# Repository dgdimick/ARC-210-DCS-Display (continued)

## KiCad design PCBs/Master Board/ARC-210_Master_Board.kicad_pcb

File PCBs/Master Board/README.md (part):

# ARC-210 Main Board v1.1 and schematic

**Last updated: November 13, 2026 at 9:41 PM MST (America/Denver)**

Updated October 29, 2026: USB-powered design with TFT VCC supplied directly from the Teensy's 3.3 V rail.

## Download and open

Download this repository using **Code → Download ZIP**, extract it, and keep this entire folder together. Open `ARC-210_Master_Board.kicad_pro` in **KiCad 10**, then open the schematic or PCB Editor.

You can also download the [schematic](ARC-210_Master_Board.kicad_sch) and [PCB v1.1](ARC-210_Master_Board.kicad_pcb) directly. Downloading only that file does not include the project library configuration.

Main Board **v1.1** includes the completed placement and routing, GND copper pours on both layers, and a [Gerber/drill package](Manufacturing/Main-Board-PCB-v1.1-Gerbers-Drill.zip). Its switch mounting and anti-rotation cutouts, four 3.5 mm mounting holes and USB zip-tie slots are retained. All 13 circuit component footprints are on B.Cu, facing away from the faceplate. ERC, DRC and schematic/PCB parity pass under the saved settings, with zero unconnected items. I’ve checked the physical fit of Main Board v1.1; current verification, assembly and manufactured-board testing are still ahead. Take your time with the build. If you get stuck, I’m happy to help in [Discussions](https://github.com/dgdimick/ARC-210-DCS-Display/discussions) if you need a hand.

## PCB layout — five or six boards

The panel uses **five required PCBs**: one Main Board, one Button Matrix, one Rotary Encoder, and two multi-position Rotary Switch boards, all controlled by one Teensy 4.1. An **optional SQL On/Off switch PCB brings the total to six**; it can be omitted when wiring directly to the switch’s solder lugs. The optional SQL board uses the same Rotary Switch PCB design.

The [shaft spacer v.5](../../Supporting%20STL%27s/Shaft_Spacer_v.5.stl) is **required in all installations** to support the longer SQL On/Off switch shaft, whether or not the optional PCB is fitted.

## Signals and connectors

- **J1:** TFT connector. See the [TFT cable mapping](../../parts/README.md#pin-headers-and-mating-connectors--october-12-2026); it is not a straight-through cable.
- **J2:** separate 4 × 4 button matrix; pins 1–4 use GPIO 30, 31, 32, 33, and pins 5–8 use GPIO 35, 36, 37, 40.
- **J4:** 14-pin rotary-encoder connector; pins 13 and 14 are GND.
- **J10 (MASTER) pin 2:** rotary-switch signal through R1 to GPIO 14 / A0, KiCad U1 pad 36.
- **J9 (MODE) pin 2:** rotary-switch signal through R2 to GPIO 15 / A1, KiCad U1 pad 37.
- **SQL1:** pin 1 is GPIO 41 / U1 pad 33; pin 2 is GND. The SQL On/Off switch PCB is optional when wiring its solder lugs directly. Dedicated **TP1 (SQL signal, GPIO 41 / U1 pad 33)** and **TP2 (GND)** solder-wire pads are now included in the Main Board schematic and PCB draft. The optional SQL1 header remains available. The pads are placed and routed in the current draft; I’ve checked the physical fit of Main Board v1.1; I still need to check the assembled board.

**GPIO labels are not KiCad pad numbers.** For example, GPIO 4 is U1 pad 6, GPIO 14 is pad 36, and GPIO 15 is pad 37. Use the labels printed on the Teensy for wiring and firmware; use the matching symbol and `teensy:Teensy41` footprint when updating the PCB.

## USB cable zip-tie slots

**Added October 29, 2026:** The PCB includes two **4 × 2 mm oblong internal cutouts** below the Teensy's USB connector. Their centers align with the two Teensy pin rows, at X = 128.21 mm and 143.45 mm, Y = 163.50 mm in the KiCad board coordinates. The long direction follows the pin rows/cable direction.

The slots are intended for a small **2.5 mm zip tie** to hold the USB cable against the PCB and reduce strain on the Teensy's Micro-B connector. They are milled cutouts on **Edge.Cuts**, with no electrical pads. The existing routing and component positions are unchanged.

**Pending physical fit check:** Confirm the actual cable plug, boot, and tie fit before final assembly. Secure the cable without loading the USB connector, leave service slack, and avoid overtightening. Final cable support validation and any additional printed support remain pending. Main Board v1.1 fabrication files are published; the physical strain-relief check remains pending.

The updated DRC/parity report shows **zero violations, zero unconnected items, and zero schematic/PCB mismatches** under the saved settings.

## Required Rotary Encoder spacers

Print **six [Rotary Encoder spacers v.1](../../Supporting%20STL%27s/Rotary_Encoder_Spacer_v.1.stl)**, one for each encoder, to center the encoder threads in the faceplate holes.

## SQL On/Off rotary switch support

Use the [shaft support spacer v.5](../../Supporting%20STL%27s/Shaft_Spacer_v.5.stl) in **all installations** to support the **longer shaft used by the SQL On/Off rotary switch**. Fit the spacer whether using the optional switch PCB or wiring directly to the switch's solder lugs.

## Channel and SQL knobs

**The 17-part set has passed test fitting at 100% scale, with Channel v4.2 separately reprinted and confirmed after the earlier complete-layout test. The combined downloads now include that replacement.** Please keep checking [Project Updates](../../Docs/Project-Updates.md) for changes.

[Channel knob v4.2](../../Supporting%20STL%27s/Channel_Knob_v.4.2.stl) · [SQL knob v1.2](../../Supporting%20STL%27s/SQL_Knob_v.1.2.stl)

**Channel v4.2 and SQL v1.2 have the same outside size and small side hole, but different shaft holes.** Print one of each at 100% scale. I’ve test-fitted both; see the [STL README](../../Supporting%20STL%27s/README.md) for the socket details and current downloads.

The SQL shaft support spacer v.5 remains required in all installations.

## Power and lighting

The Teensy is powered by USB, and **TFT VCC connects directly to the Teensy's 3.3 V rail** (`TEENSY_3V3`, U1 pad 15). I’ve tested the TFT at 3.3 V and found the brightness satisfactory. I removed the external protected 5 V input and Main Board JP1 power selector. I removed C5 (470 µF) and C6 (0.1 µF) to match the direct Teensy-to-TFT wiring I tested. C1/C2 and R1/R2 remain as the rotary-input filters. Keep total external 3.3 V consumption within PJRC's recommended 250 mA maximum; brightness confirmation is not a current measurement.

Removed from the schematic and PCB: **J3, F2, D1, D2, D3, Q2, R15, R16, R17, JP1, C5, and C6**. There is no external input jack, fuse, SCR/zener protection branch, power indicator LED, or TFT power-selector shunt in this revision. This does not affect the separate rotary-switch PCB's JP1 solder bridge.

C5 (470 µF) and C6 (0.1 µF) have been removed from the schematic, PCB, and BOM to match the tested direct TFT wiring. No additional TFT supply capacitors are fitted on this Main Board. C1/C2 and R1/R2 remain as the rotary-input filters. The TFT backlight-control signal remains connected to GPIO 4.

**The current Button Matrix PCB v3.2 does not support LED backlighting.** I would need to redesign it and the Main Board and use light-transmitting buttons. There is no finished design or release date. The TFT backlight is separate; see [Future Thoughts](../../Docs/Future-Thoughts.md) for clearance, power, possible four-layer costs, and reusable-part plans.

My aim is to reuse the **rotary encoders, rotary switches, socket-mounted Teensy, faceplate, and other compatible parts outside the two replacement boards**. I still need to check compatibility during the redesign. Male Teensy headers and matching Main Board sockets would let you move the controller to a compatible replacement board. Illuminated legends would need suitable light-transmitting buttons.

## Rotary-switch test wiring

I tested both seven-position switches with their outputs connected directly to GPIO 14 and 15. They worked without the schematic's 220 Ω series resistors or 100 nF filter capacitors. The six 1 kΩ ladder resistors on each switch board were fitted and JP1 on each switch board was open. I saw voltage fluctuations on the TFT, but they did not affect the detected switch positions.

## Teensy 4.1 in the 3D Viewer

### Main PCB 3D preview

*October 28, 2026 — Main Board placement and routing in progress, viewed from the component side facing away from the faceplate.*

The current working layout includes the Teensy 4.1, TFT and control connectors, and SQL On/Off solder connections. **J9 is MODE** (GPIO 15 / A1), and **J10 is MASTER** (GPIO 14 / A0). A **26.2 mm circle**, centered on the SQL shaft hole, provides a switch-body spacing guide without electrical pads. The earlier board-edge silkscreen clipping warning is resolved in the corrected upload. The existing shaft opening, anti-rotation slot, and mounting holes are retained.

The current saved PCB and schematic shown by this layout-progress update are now uploaded to this folder. The v1.1 design checks pass under the saved settings. I’ve checked the physical fit of Main Board v1.1; I still need to complete verification. Main Board v1.1 design and fabrication files are now published; physical fit is confirmed and manufactured-board validation is still to come.

[Earlier angled Teensy 4.1 preview — October 27](../../images/Main-PCB-Teensy-3D.png)

The project includes [Teensy_4.1_Board.step](Libraries/3dmodels/Teensy_4.1_Board.step), already attached to **U1** in the Main PCB. Its model path is `${KIPRJMOD}/Libraries/3dmodels/Teensy_4.1_Board.step`, so it works after downloading or cloning the repository without a machine-specific path.

1. Download the repository ZIP or clone it, then extract/keep the entire Main Board project folder together.
2. Open `ARC-210_Master_Board.kicad_pro` and launch PCB Editor.
3. Open **View → 3D Viewer** (**Alt+3**).
4. Rotate to the back/underside: U1 and the other component bodies are on **B.Cu**, facing away from the faceplate.

If U1 is missing, check its **Footprint Properties → 3D Models** entry and confirm the STEP file is present at the path above. Reopen the viewer after replacing project files. The old missing assembly-model path and erroneous footprint-folder model entry have been removed.

I checked the model in bottom and angled renders. This verifies visibility and visual alignment; I’ve now checked the physical fit of Main Board v1.1. Final socket height and component clearances should still be checked during assembly. No electrical connections were changed by attaching the model.

## Included libraries and checks

- `Libraries/symbols/teensy.kicad_sym`: Teensy symbols; accompanying license included.
- `Libraries/symbols/ARC210_Power.kicad_sym`: C106D SCR symbol.
- `Libraries/teensy.pretty/Teensy41.kicad_mod`: matching Teensy 4.1 footprint.
- `ARC210_Custom.pretty`: historical custom footprints; the removed protection parts are no longer fitted.
- `sym-lib-table` and `fp-lib-table`: project-relative library paths.

Install KiCad's standard symbol, footprint, and 3D model libraries too. The Teensy 4.1 STEP model is now included and attached to U1; see the 3D Viewer section above.

October 29, 2026 checks after matching J4 and TP1 values: [ERC](ERC-report.json) reports **zero violations**. [PCB DRC and schematic parity](DRC-report.json) report **zero DRC violations, zero unconnected items, and zero schematic/PCB mismatches** under the saved settings. J4 is labelled **ROTARY ENCODERS** and TP1 **SQL ON/OFF** in both the schematic and PCB. The silkscreen clipping warning is also resolved. Some check categories are disabled. Physical fit is confirmed for Main Board v1.1. Final routing review and current verification remain pending; the v1.1 fabrication files are published, with board fit confirmed and assembled-board validation still pending.

PCB design license: CERN-OHL-P-2.0, as specified in the [main README](../../README.md#licensing). The bundled Teensy library retains its included license.

## Build cost and community

See the [DIY parts purchasing estimate](../../parts/README.md#estimated-build-cost) to plan your budget. This is primarily a DIY project, with files and guidance to help you source parts and fabrication independently.

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
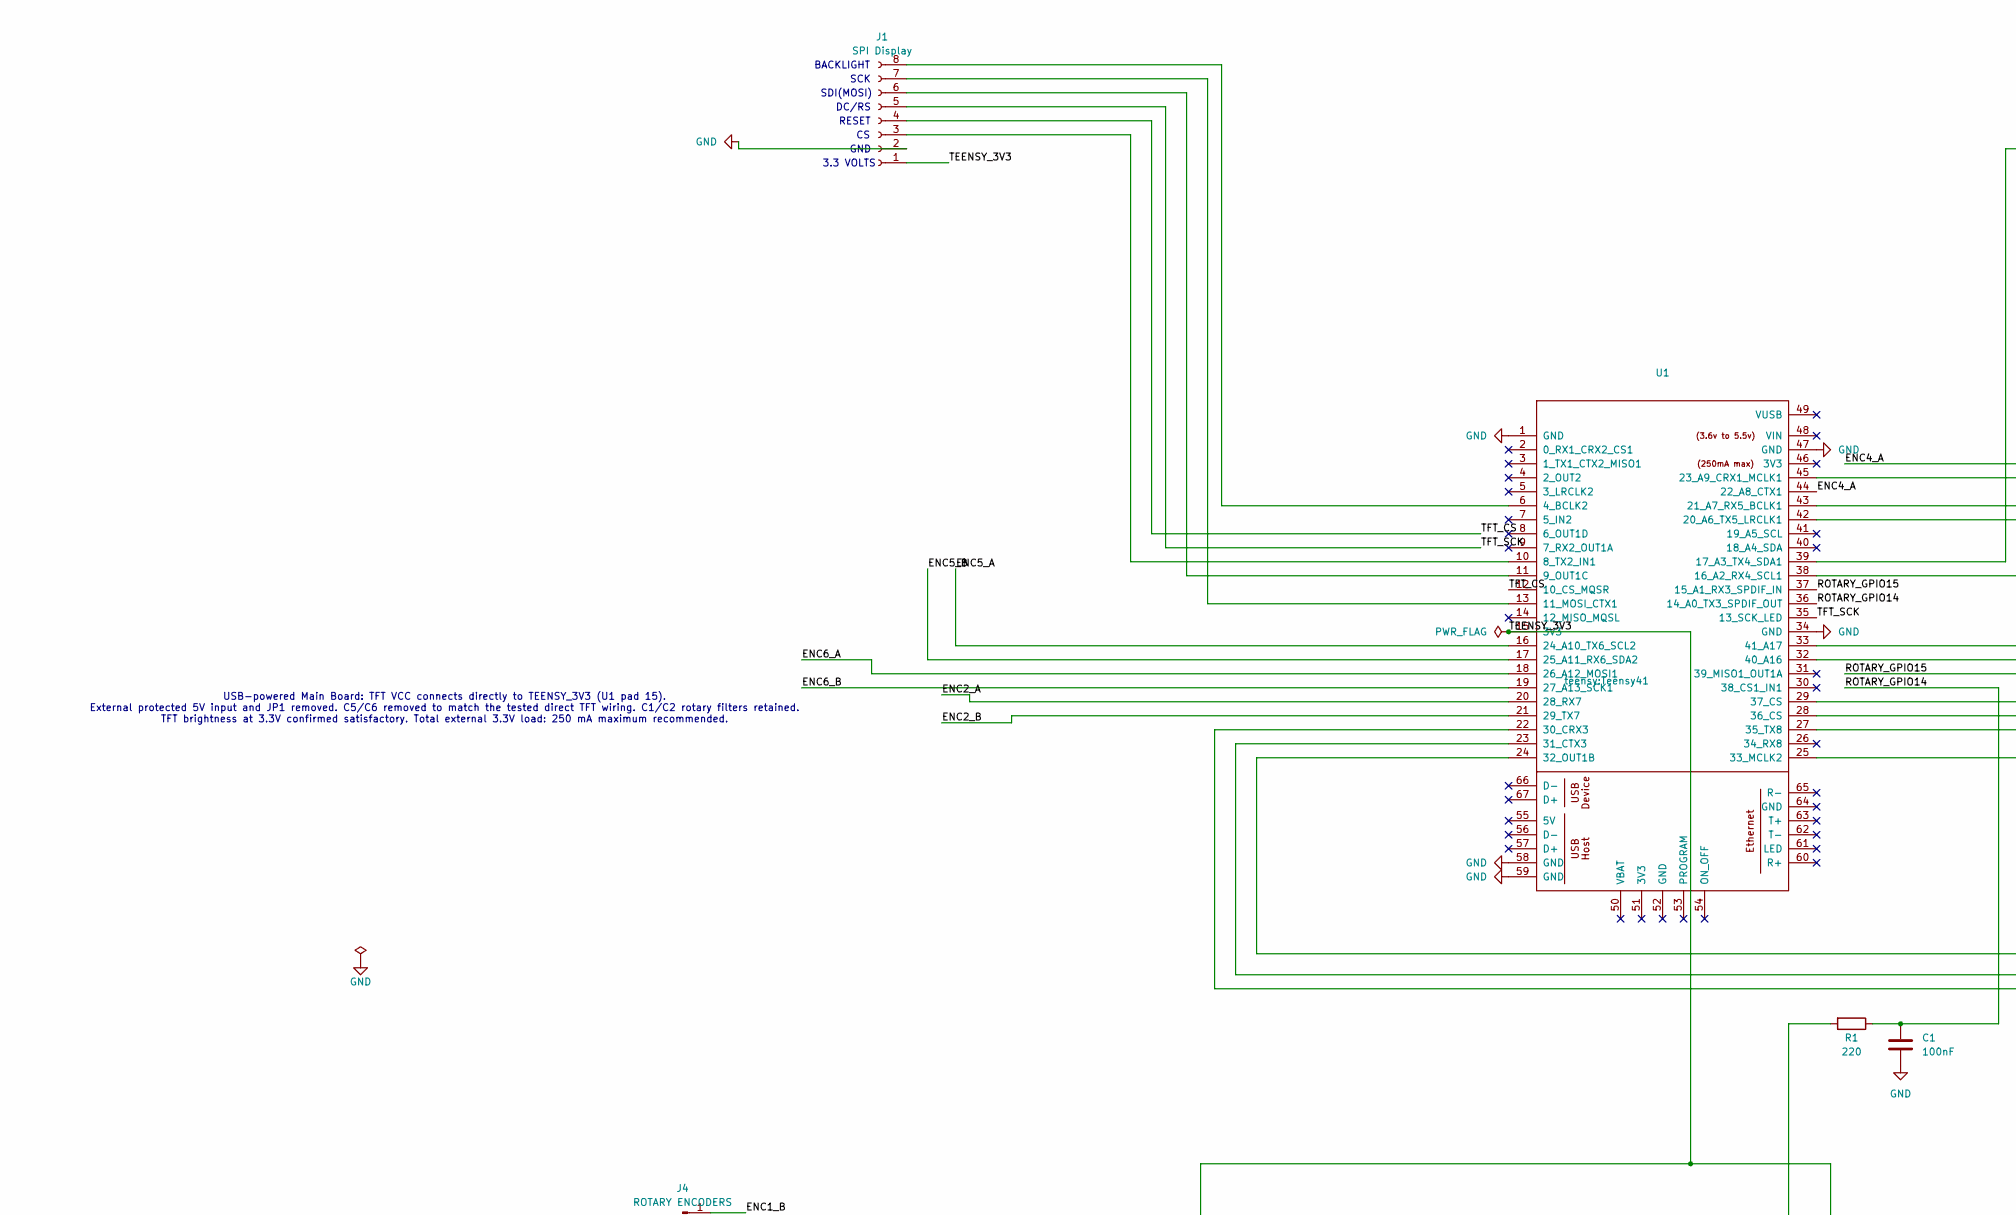
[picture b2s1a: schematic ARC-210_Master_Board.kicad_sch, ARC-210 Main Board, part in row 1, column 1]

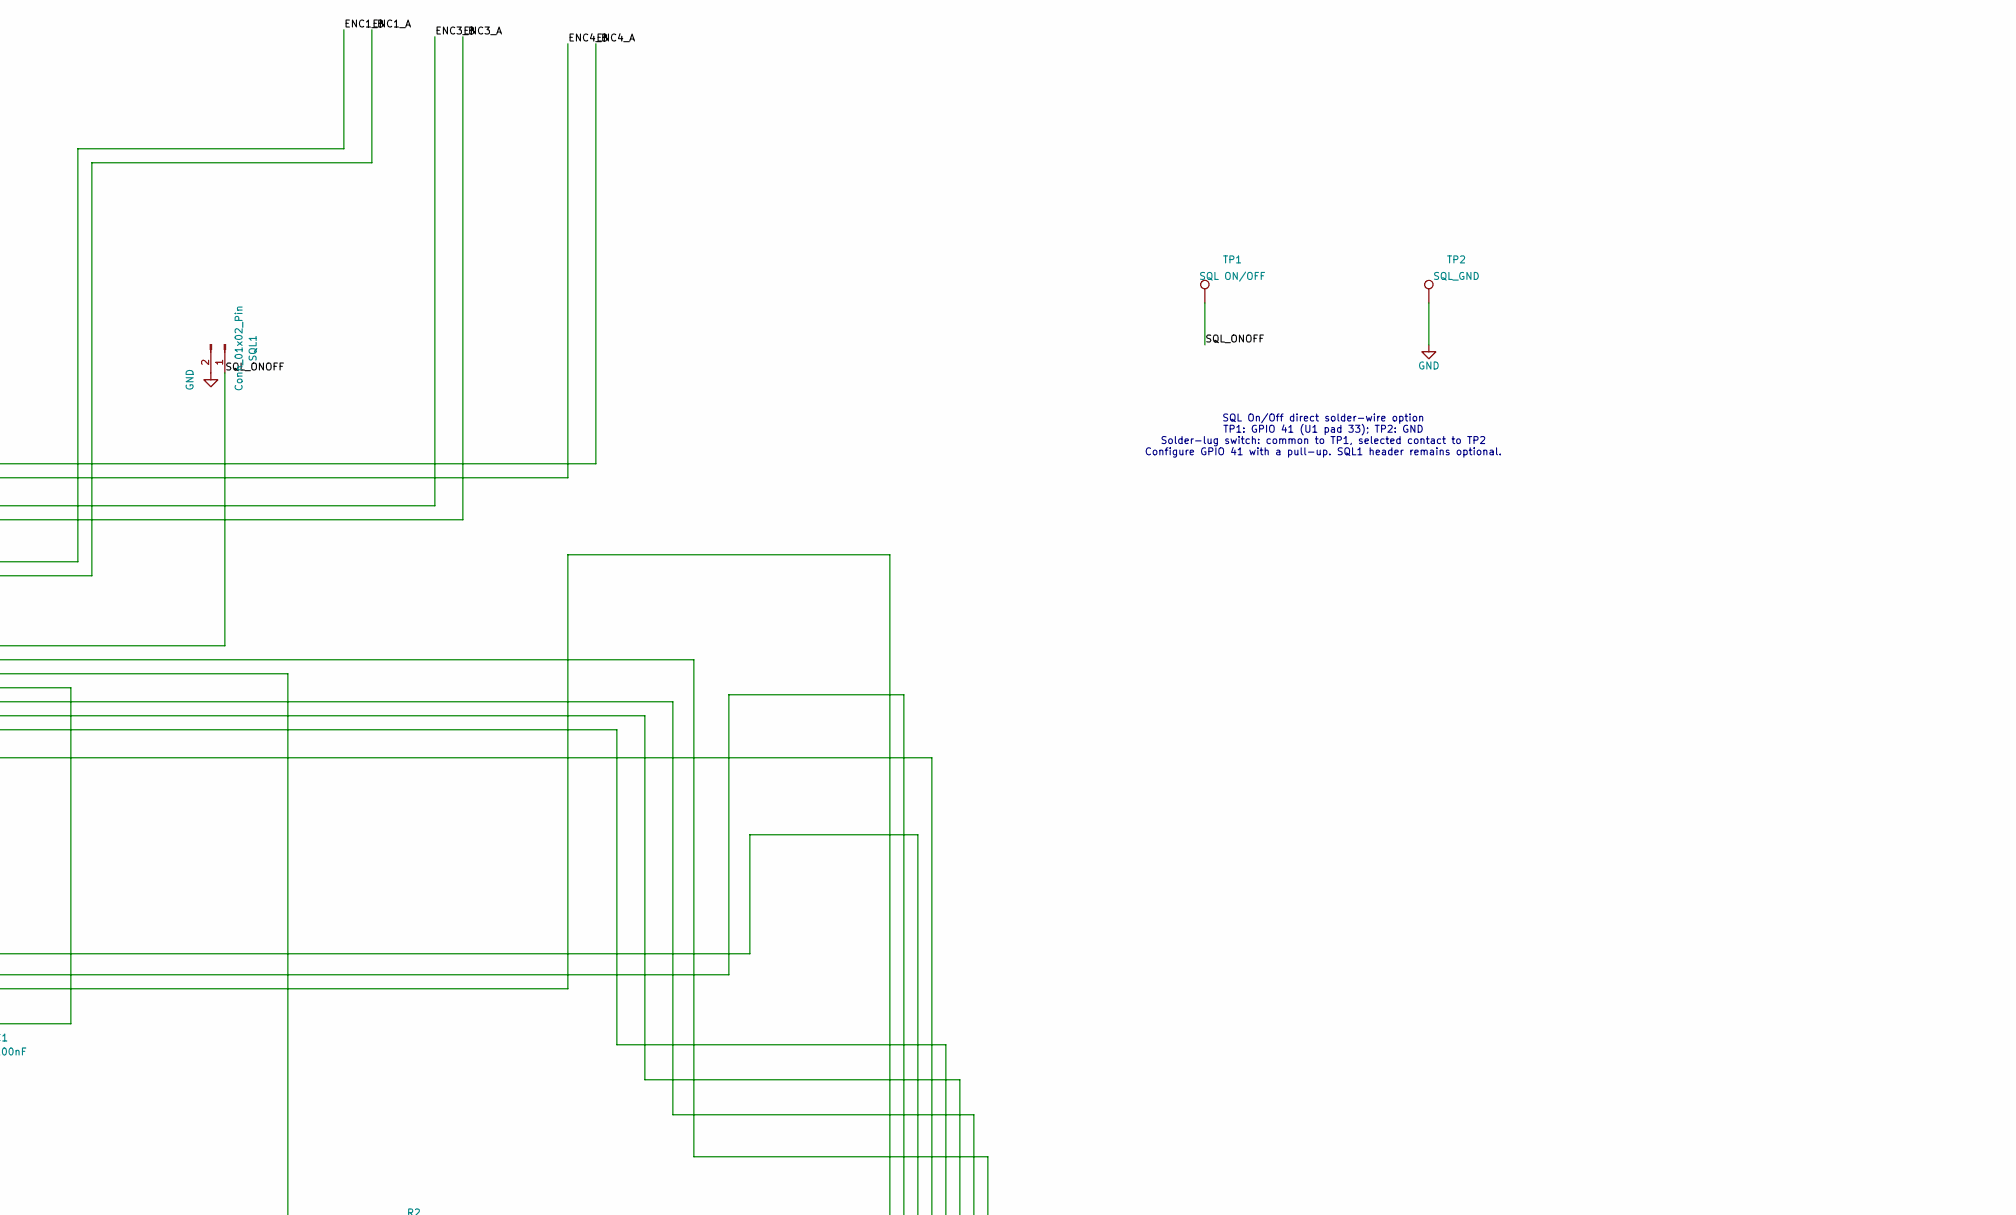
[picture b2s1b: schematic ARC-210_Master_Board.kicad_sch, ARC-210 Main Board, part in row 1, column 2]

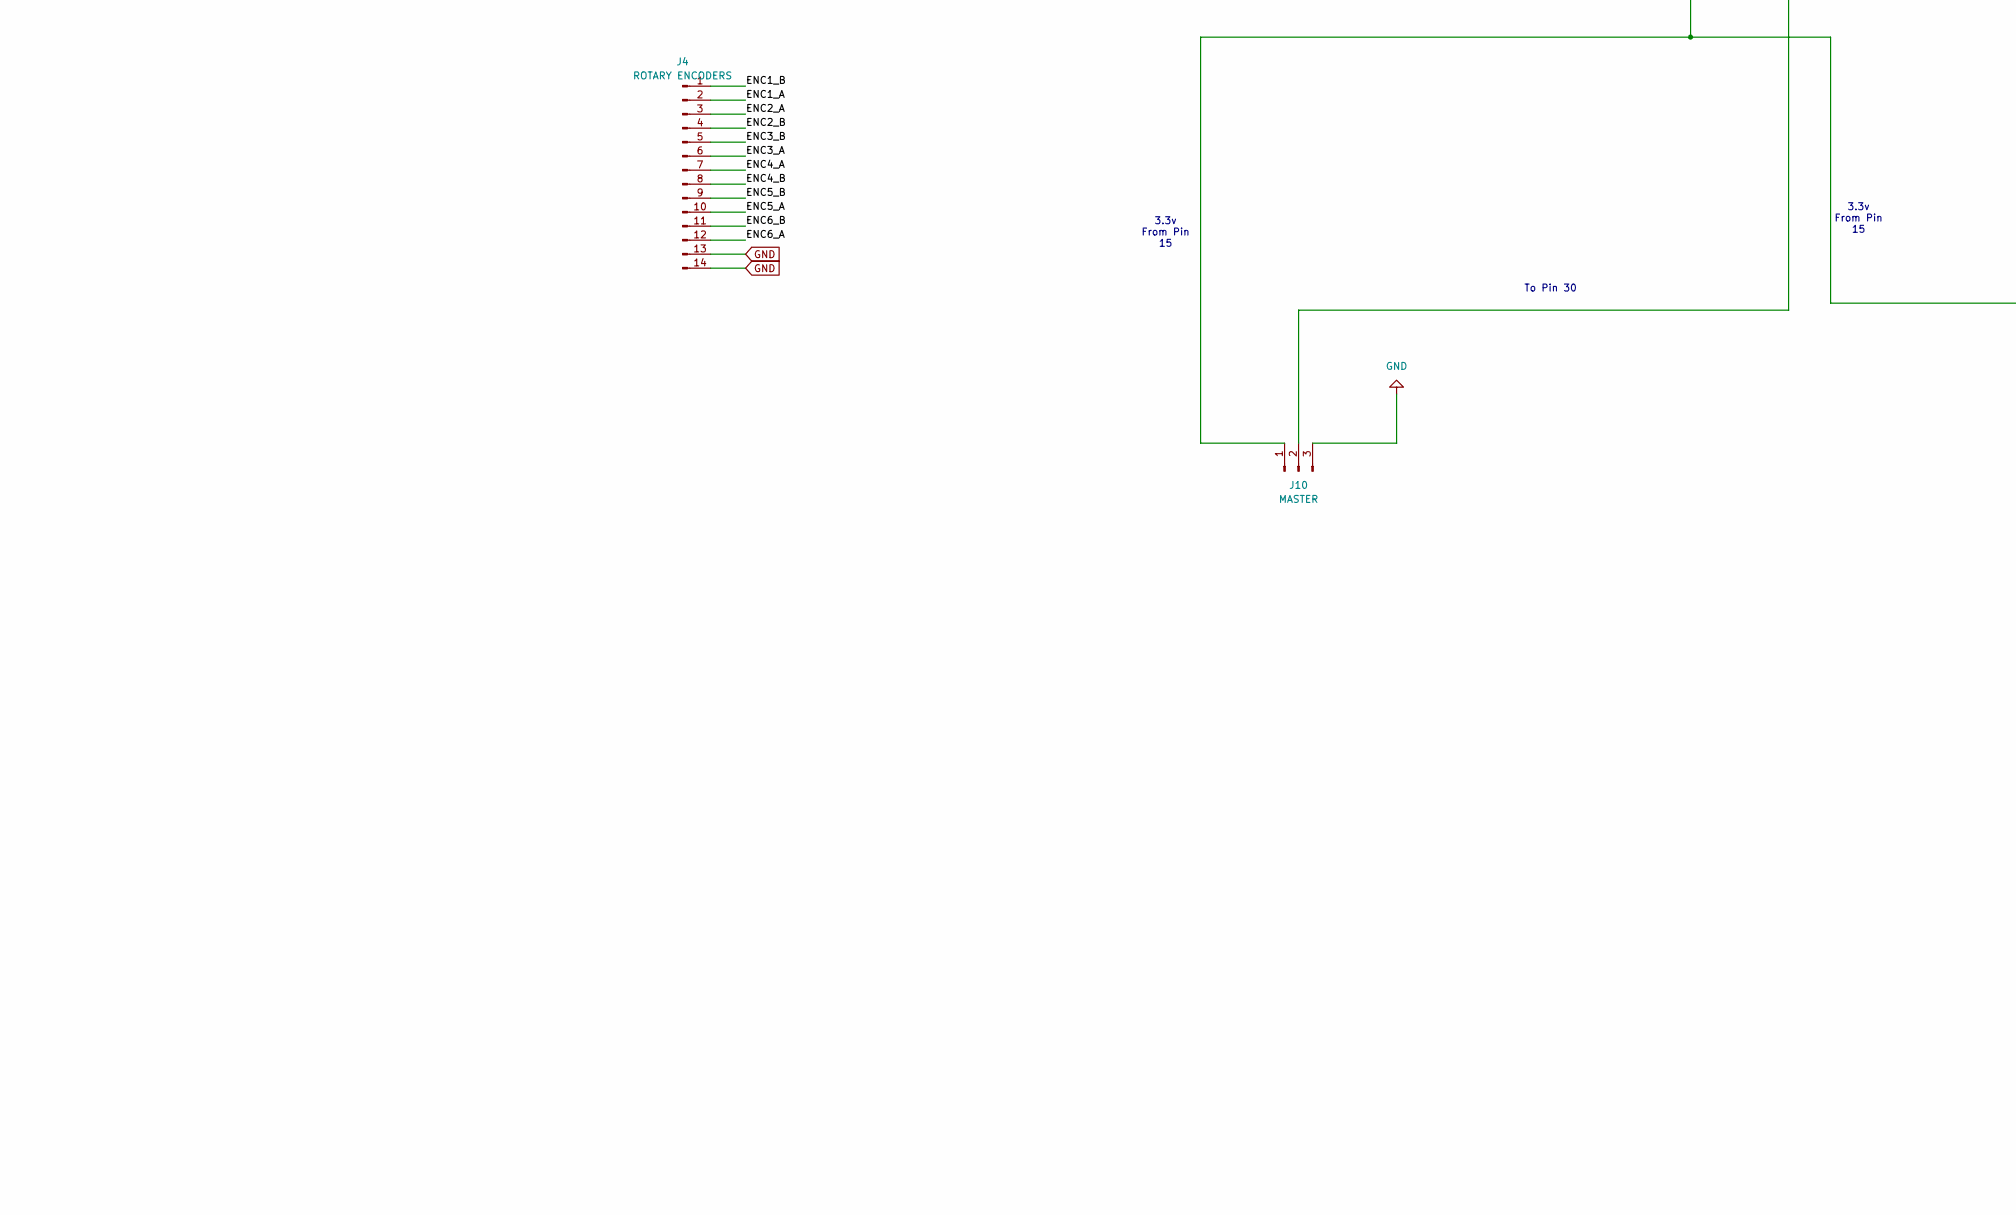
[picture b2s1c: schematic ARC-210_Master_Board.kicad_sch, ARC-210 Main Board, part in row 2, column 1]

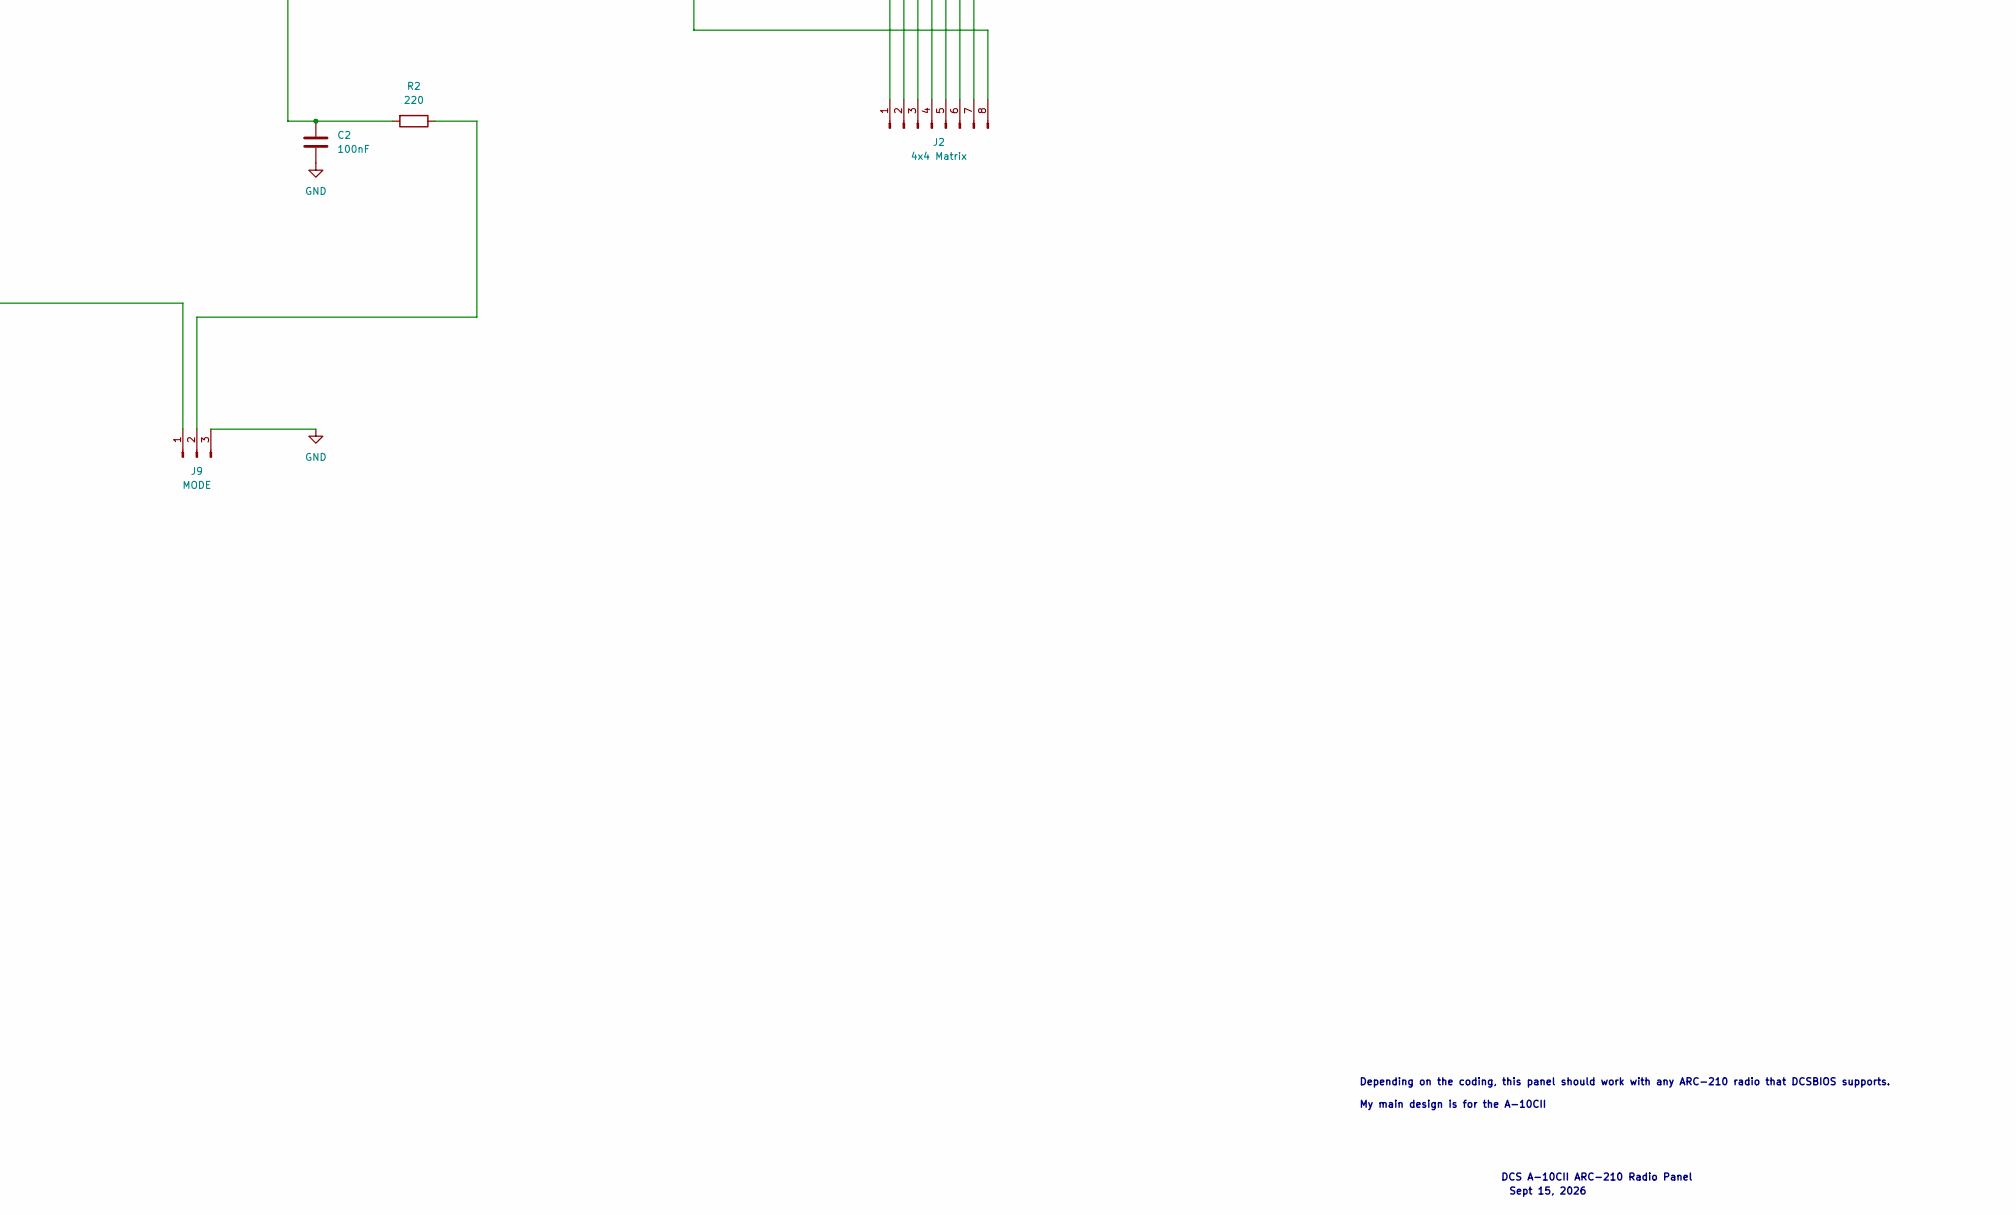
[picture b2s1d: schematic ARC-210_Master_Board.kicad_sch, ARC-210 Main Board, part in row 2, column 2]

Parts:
C1, C2: 100nF; C_Disc_D5.0mm_W2.5mm_P2.50mm
J1: SPI Display; PinHeader_1x08_P2.54mm_Vertical
J2: 4x4 Matrix; PinHeader_1x08_P2.54mm_Vertical
J4: ROTARY ENCODERS; PinHeader_1x14_P2.54mm_Vertical
J9: MODE; PinHeader_1x03_P2.54mm_Vertical
J10: MASTER; PinHeader_1x03_P2.54mm_Vertical
R1, R2: 220; R_Axial_DIN0204_L3.6mm_D1.6mm_P5.08mm_Horizontal
SQL1: Conn_01x02_Pin; PinHeader_1x02_P2.54mm_Vertical
TP1: SQL ON/OFF; TestPoint_THTPad_D3.0mm_Drill1.5mm
TP2: SQL_GND; TestPoint_THTPad_D3.0mm_Drill1.5mm
U1: Teensy4.1; Teensy41

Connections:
/ENC1_A: J4.2, U1.38 (16_A2_RX4_SCL1)
/ENC1_B: J4.1, U1.39 (17_A3_TX4_SDA1)
/ENC2_A: J4.3, U1.20 (28_RX7)
/ENC2_B: J4.4, U1.21 (29_TX7)
/ENC3_A: J4.6, U1.42 (20_A6_TX5_LRCLK1)
/ENC3_B: J4.5, U1.43 (21_A7_RX5_BCLK1)
/ENC4_A: J4.7, U1.44 (22_A8_CTX1)
/ENC4_B: J4.8, U1.45 (23_A9_CRX1_MCLK1)
/ENC5_A: J4.10, U1.16 (24_A10_TX6_SCL2)
/ENC5_B: J4.9, U1.17 (25_A11_RX6_SDA2)
/ENC6_A: J4.12, U1.18 (26_A12_MOSI1)
/ENC6_B: J4.11, U1.19 (27_A13_SCK1)
/ROTARY_GPIO14: C1.2, R1.1, U1.36 (14_A0_TX3_SPDIF_OUT)
/ROTARY_GPIO15: C2.1, R2.2, U1.37 (15_A1_RX3_SPDIF_IN)
/SQL_ONOFF: SQL1.1, TP1.1 (1_1), U1.33 (41_A17)
/TEENSY_3V3: J1.1, J9.1, J10.1, U1.15 (3V3)
/TFT_CS: J1.4, U1.12 (10_CS_MQSR)
/TFT_SCK: J1.5, U1.35 (13_SCK_LED)
GND: C1.1, C2.2, J1.2, J4.13, J4.14, J9.3, J10.3, SQL1.2, TP2.1 (1_1), U1.1 (GND), U1.34 (GND), U1.47 (GND), U1.58 (GND), U1.59 (GND)
unnamed: J1.3, U1.10 (8_TX2_IN1)
unnamed: J1.6, U1.11 (9_OUT1C)
unnamed: J1.7, U1.13 (11_MOSI_CTX1)
unnamed: J1.8, U1.6 (4_BCLK2)
unnamed: J2.1, U1.22 (30_CRX3)
unnamed: J2.2, U1.23 (31_CTX3)
unnamed: J2.3, U1.24 (32_OUT1B)
unnamed: J2.4, U1.25 (33_MCLK2)
unnamed: J2.5, U1.27 (35_TX8)
unnamed: J2.6, U1.28 (36_CS)
unnamed: J2.7, U1.29 (37_CS)
unnamed: J2.8, U1.32 (40_A16)
unnamed: J9.2, R2.1
unnamed: J10.2, R1.2

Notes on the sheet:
SCK
Sept 15, 2026
BACKLIGHT
USB-powered Main Board: TFT VCC connects directly to TEENSY_3V3 (U1 pad 15). External protected 5V input and JP1 removed. C5/C6 removed to match the tested direct TFT wiring. C1/C2 rotary filters retained. TFT brightness at 3.3V confirmed satisfactory. Total external 3.3V load: 250 mA maximum recom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
3.3 VOLTS
SQL On/Off direct solder-wire option TP1: GPIO 41 (U1 pad 33); TP2: GND Solder-lug switch: common to TP1, selected contact to TP2 Configure GPIO 41 with a pull-up. SQL1 header remains optional.
DCS A-10CII ARC-210 Radio Panel
SDI(MOSI)
3.3v From Pin 15
DC/RS
To Pin 30
GND
RESET
Depending on the coding, this panel should work with any ARC-210 radio that DCSBIOS supports. My main design is for the A-10CII

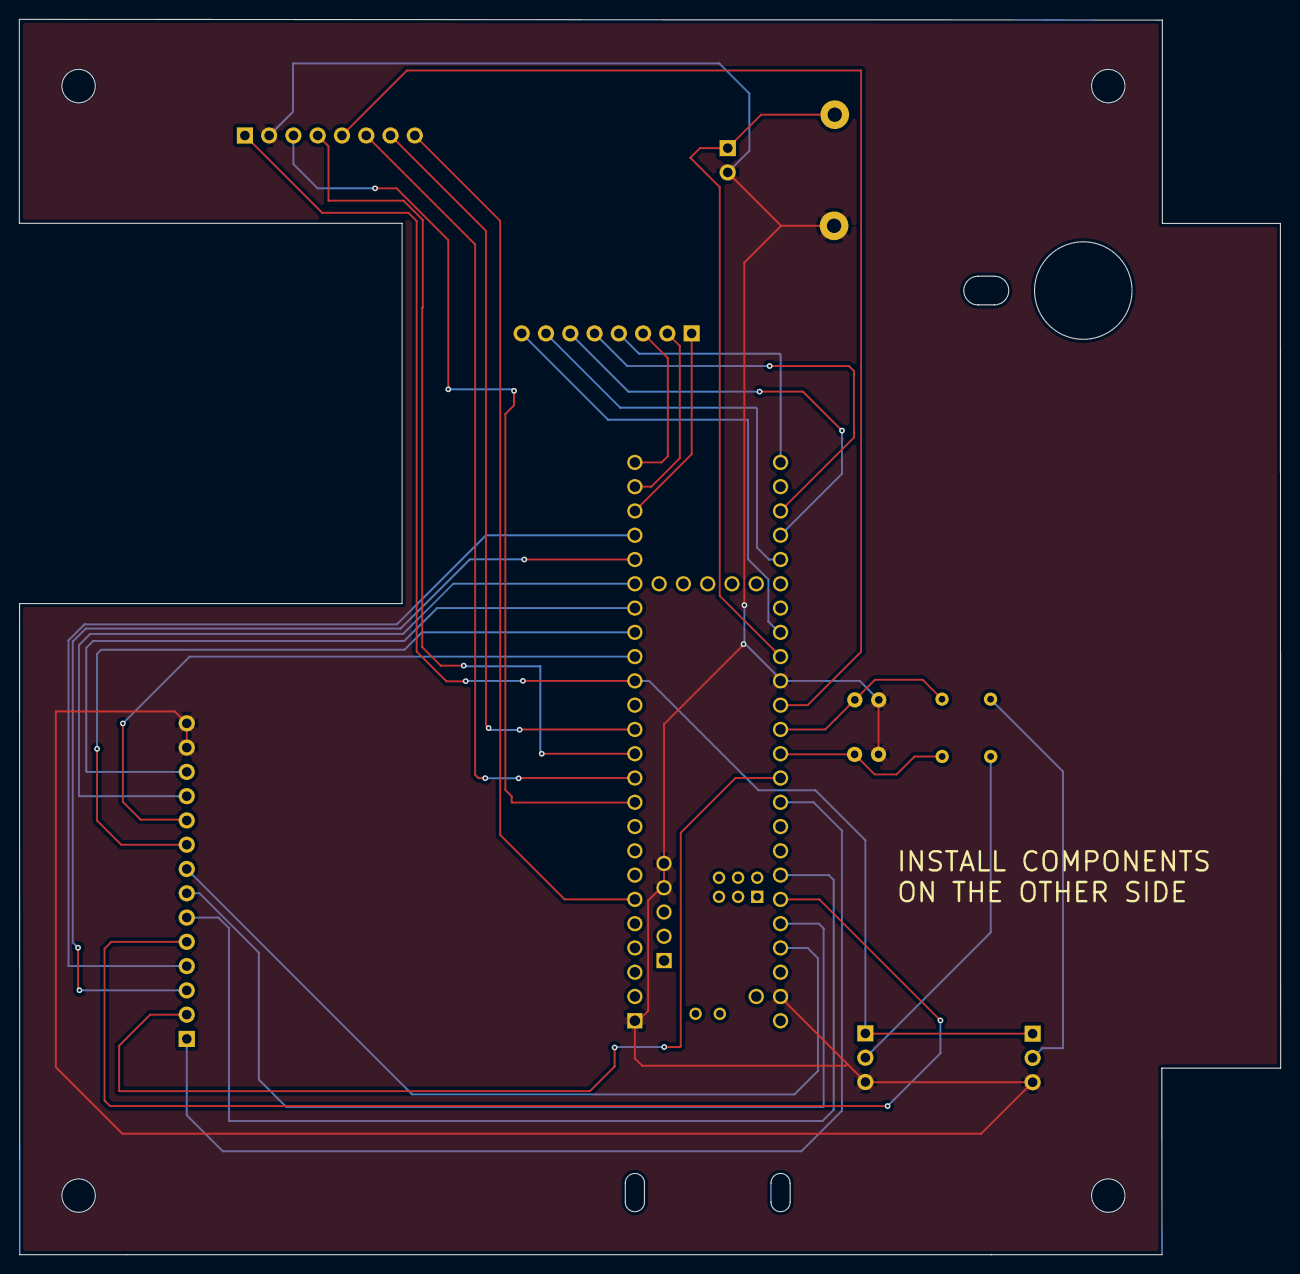
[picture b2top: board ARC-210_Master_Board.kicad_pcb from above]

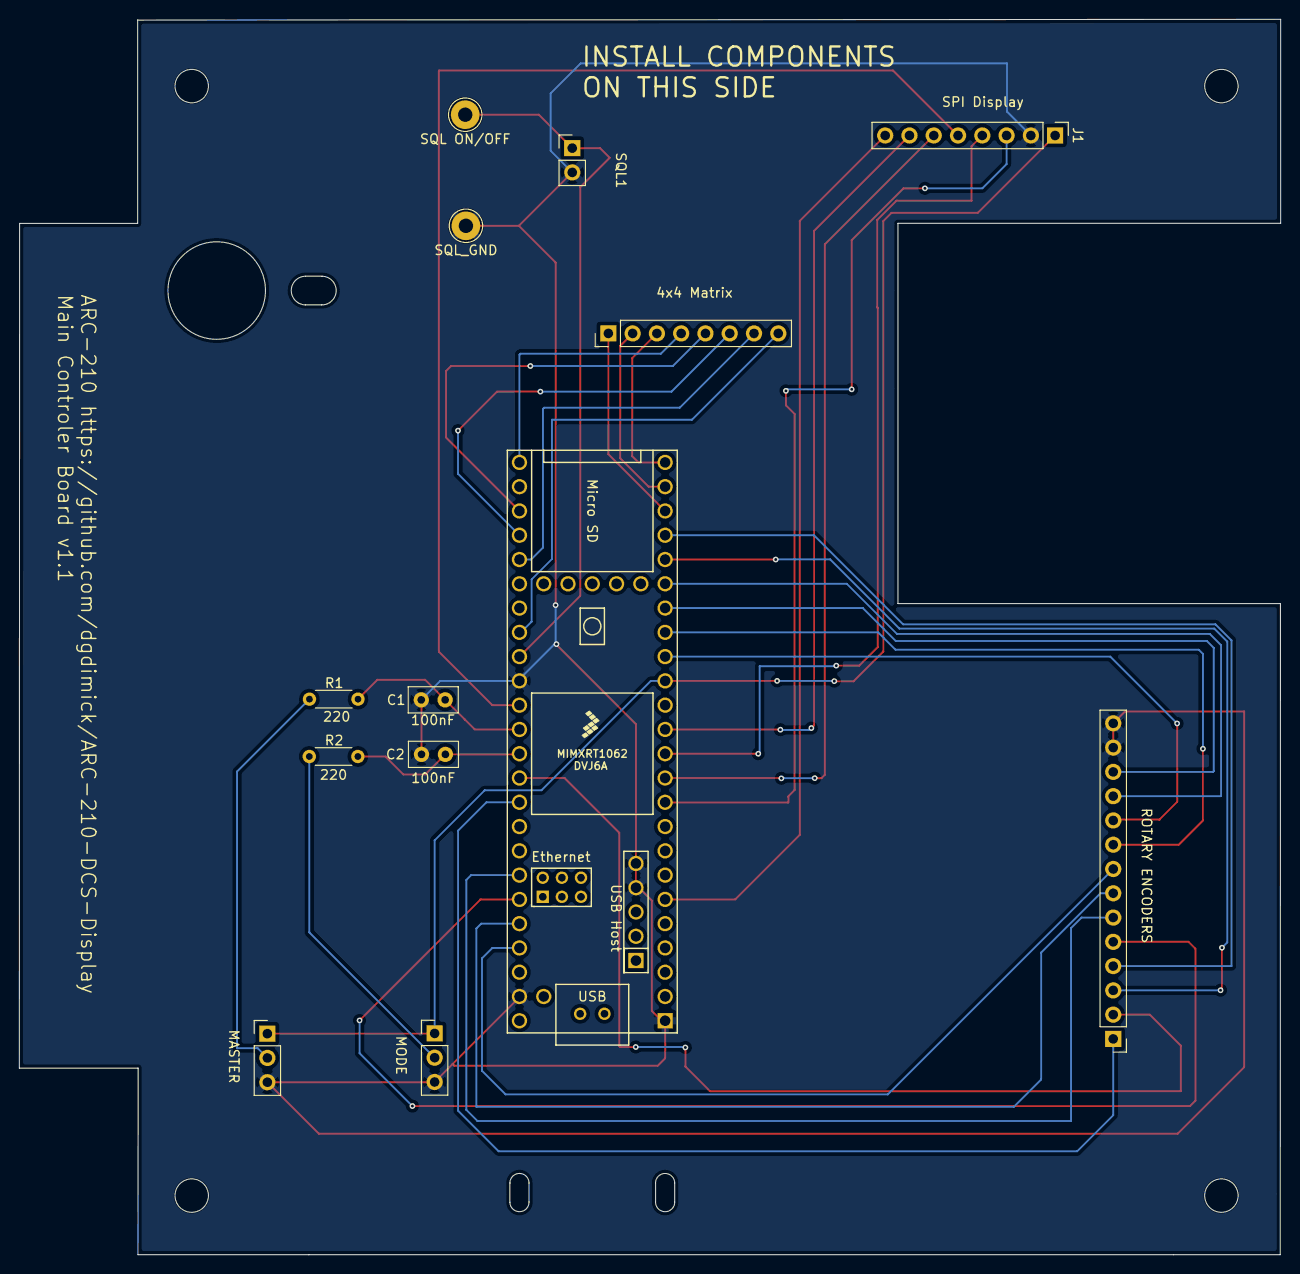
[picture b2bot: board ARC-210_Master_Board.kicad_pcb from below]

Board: 2 copper layers, 132.0 x 129.2 mm, 17 parts (13 on the bottom side), 33 nets.

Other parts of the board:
H1, H2, H4, H5: MountingHole_3.5mm

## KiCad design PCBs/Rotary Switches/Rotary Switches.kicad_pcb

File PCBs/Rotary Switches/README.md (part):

# ARC-210 Rotary Switch PCB — Version 2.0 — Final PCB design

**Last updated: November 13, 2026 at 9:41 PM MST (America/Denver)**

Updated October 12, 2026.

Version **2.0 is the final PCB design and has been physically test-fitted**, confirmed October 12, 2026.

Version 2.0 uses a 27.99 mm circular PCB outline, approximately 1 mm outside the switch body, with the resistors and connector repositioned inside the outline. The PCB silkscreen and board revision identify version 2.0. This project replaces the previously published board. Switch terminal 1 is used for position 1. The resistor ladder uses **six resistors (R1–R6)** to provide seven switch-position voltages. The switch contacts used are 1, 2, 4, 5, 7, 8 and 10; terminal 11 is unused. A1 is the common contact and analog output.

Open `Rotary Switches.kicad_pro`. The project includes its custom symbol and A12505RNCQ footprint, with relative library paths so they work after downloading.

- SW1: C&K A12505RNCQ, PCB terminals, 12.7 mm shaft, 45° indexing.
- R1–R6: **six resistors**, each 1 kΩ, 1%, 1/8 W.
- J1: pin 1 = 3.3 V; pin 2 = analog output; pin 3 = GND.

The Main Board schematic shows a 220 Ω series resistor and 100 nF capacitor near each Teensy rotary-switch input.

**Tested wiring:** I tested both seven-position rotary switches, and they worked with each switch PCB’s J1 pin 2 connected directly to its Teensy input (GPIO 14 or GPIO 15), without the 220 Ω series resistor or 100 nF input-filter capacitor. The six 1 kΩ resistor-ladder resistors on each switch PCB were still fitted, and JP1 was left open. I saw some fluctuation in the TFT voltage readings, but it did not affect the detected switch positions. This records the successful breadboard setup; the input-filter components shown in the Main Board schematic were not part of that test.

## SQL On/Off option added in version 1.2

**SQL On/Off:** I use the **C&K A12515RNZQ solder-lug rotary switch**, with its stop ring set to **two positions for 45° total travel**. Align the knob with the panel’s ON/OFF markings. See the [parts list](../../parts/README.md) for shaft-length and mounting details.

The **SQL On/Off PCB is optional**: use it for the switch wiring, or omit it and wire directly to the switch’s solder lugs as described below. The panel uses five required boards, or six with this optional SQL board.

The [shaft spacer v.5](../../Supporting%20STL%27s/Shaft_Spacer_v.5.stl) is **required in all installations** to support the **longer SQL On/Off switch shaft**, whether or not the optional PCB is fitted.

I modified the PCB so it can also be used with the SQL On/Off switch. **JP1**, marked **ON/OFF** on the back of the PCB near R2, is an open solder jumper between GND and the R1–R2 junction: R2 pad 1, also connected to switch terminal 2.

- **SQL On/Off:** omit all six resistors R1–R6 and bridge JP1 with solder. Connect J1 pin 2 (switch common A1) to a Teensy input configured with a pull-up, and J1 pin 3 to GND. Selecting terminal 2 pulls the input LOW; an ungrounded contact reads HIGH. J1 pin 1 is not needed for this configuration. Choose the contact for the intended electrical ON/OFF states. Set the stop ring to **two positions with 45° total travel**.
- **Resistor ladder:** fit all six resistors R1–R6 and leave JP1 open. Use the three J1 connections listed above.

The solder-lug A12515RNZQ still requires mechanical support and wires to the corresponding PCB connections; it does not fit the PCB-pin footprint directly.

## MAIN and MOD rotary switches

### Check the resistor ladder before installing the switch

1. Solder all six 1 kΩ resistors (R1–R6) and the J1 pin header first. Leave JP1 open. Bend one lead of each resistor back alongside its body so the resistor stands upright. Put the two leads into the pair of small holes next to each other for that resistor. Resistors have no polarity, so either lead can go in either hole of the pair. If you’re unsure which holes to use, [ask me in Discussions](https://github.com/dgdimick/ARC-210-DCS-Display/discussions). I’m happy to help.
2. With the PCB disconnected from power, set your VOM or multimeter to resistance (Ω) and touch one probe to each pad marked **Test Here**. A reading **close to 6 kΩ** checks the solder connections through all six resistors in series.
3. Once the board passes the test, solder on the rotary switch.

Validation for version 2.0: KiCad PCB DRC, with zones refilled, reported zero non-excluded violations and zero unconnected pads under the saved project settings. The project contains 15 specific PTH-inside-switch-courtyard exclusions for the rear-side resistors and connector; I checked fit on the assembled boards. Several other check categories are disabled in the project. Fresh electrical schematic and PCB checks, including schematic parity, were run October 27, 2026; see the manufacturing files section. The assembled Rotary Switch PCBs v2.0 passed both fit and functional testing.

**SQL On/Off direct-wiring option:** The SQL On/Off PCB is optional when using the solder-lug switch. You can solder wires directly to the switch’s common lug and the selected contact lug, then connect them to the Main Board’s SQL signal (GPIO 41) and GND connections. Configure GPIO 41 with a pull-up and choose the contact for the intended electrical ON/OFF states. Set the stop ring to **two positions with 45° total travel**. No resistor ladder is needed for this option. The Main Board v1.1 now includes TP1 (SQL signal, GPIO 41 / U1 pad 33) and TP2 (GND) for direct solder-wire connections. The optional SQL1 header remains; the current Main Board v1.1 is routed with zero unconnected items; physical fit is confirmed for Main Board v1.1; final routing review and assembly checks remain pending.

## Manufacturing files

Download [Rotary-Switch-PCB-v2.0-Gerbers-Drill.zip](Manufacturing/Rotary-Switch-PCB-v2.0-Gerbers-Drill.zip) for PCB fabrication. Generated October 27, 2026 from the published version **2.0** PCB using KiCad 10.0.7. [Individual Gerbers, drill files, drill maps, and check reports](Manufacturing/) are also included.

The ZIP contains seven Gerber X2 layers (front/back copper, solder mask, silkscreen, and Edge.Cuts), a Gerber job file, separate metric Excellon PTH/NPTH drill files, a drill report, and manufacturing notes. Both Gerbers and drills use the absolute origin without mirroring. The source specifies a two-layer, 1.6 mm board. Verified drill totals: **24 plated holes and zero non-plated holes**; the empty NPTH file is included intentionally.

Fresh checks reported **zero ERC violations, zero non-excluded DRC violations, zero unconnected items, and zero schematic/PCB parity issues** under the saved settings. Existing disabled checks and the 15 PTH-inside-switch-courtyard exclusions remain in effect. Review the manufacturer's preview before ordering.

## Optional switch 3D model

Download [LIB_A12505RNCQ.zip](LIB_A12505RNCQ.zip), the supplier archive for the actual **A12505RNCQ through-hole PCB-terminal switch**. Extract `A12505RNCQ/3D/A12505RNCQ.stp` and place the STP file beside `Rotary Switches.kicad_pcb`.

The board and library footprint reference `${KIPRJMOD}/A12505RNCQ.stp`. Reopen or reload the board's 3D Viewer after extraction. The board currently retains offset X = -10.5 mm, Y = 3 mm, Z = 7.5 mm, scale = 1 on all axes, and rotation X = -90°, Y = 0°, Z = 0°. These transforms were carried over from the prior model and have not been visually verified with the replacement. The reusable library footprint retains its own zero offsets and rotations; adjust those when using it for new placements.

This correct model replaces the earlier A12515RNZQ solder-lug substitute. The older ZIP is retained only as a historical optional download; use **LIB_A12505RNCQ.zip** for this PCB. No pads or electrical connections were changed by correcting the model reference.

PCB design licensing: CERN-OHL-P-2.0, as specified in the repository.

## Teensy GPIO labels and KiCad pin numbers

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
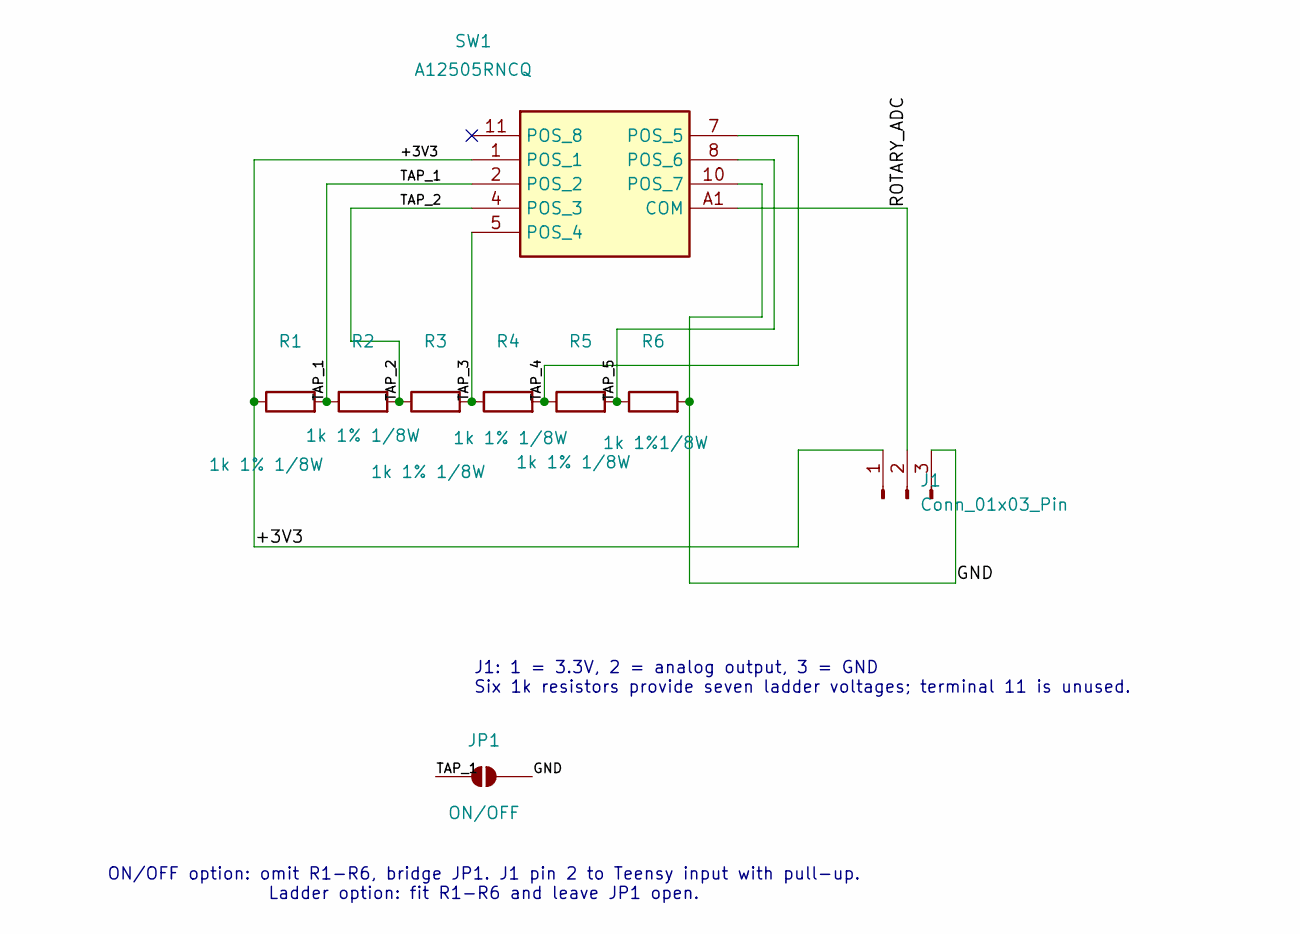
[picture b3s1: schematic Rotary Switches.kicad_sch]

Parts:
J1: Conn_01x03_Pin; PinHeader_1x03_P2.54mm_Vertical
JP1: ON/OFF; SolderJumper-2_P1.3mm_Open_Pad1.0x1.5mm
R1, R2, R3, R4, R5: 1k 1% 1/8W; R_Axial_DIN0204_L3.6mm_D1.6mm_P1.90mm_Vertical
R6: 1k 1%1/8W; R_Axial_DIN0204_L3.6mm_D1.6mm_P1.90mm_Vertical
SW1: A12505RNCQ

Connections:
/+3V3: J1.1, R1.1, SW1.1 (POS_1)
/GND: J1.3, JP1.2 (B), R6.2, SW1.10 (POS_7)
/ROTARY_ADC: J1.2, SW1.A1 (COM)
/TAP_1: JP1.1 (A), R1.2, R2.1, SW1.2 (POS_2)
/TAP_2: R2.2, R3.1, SW1.4 (POS_3)
/TAP_3: R3.2, R4.1, SW1.5 (POS_4)
/TAP_4: R4.2, R5.1, SW1.7 (POS_5)
/TAP_5: R5.2, R6.1, SW1.8 (POS_6)

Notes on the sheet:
ON/OFF option: omit R1-R6, bridge JP1. J1 pin 2 to Teensy input with pull-up. Ladder option: fit R1-R6 and leave JP1 open.
J1: 1 = 3.3V, 2 = analog output, 3 = GND Six 1k resistors provide seven ladder voltages; terminal 11 is unused.

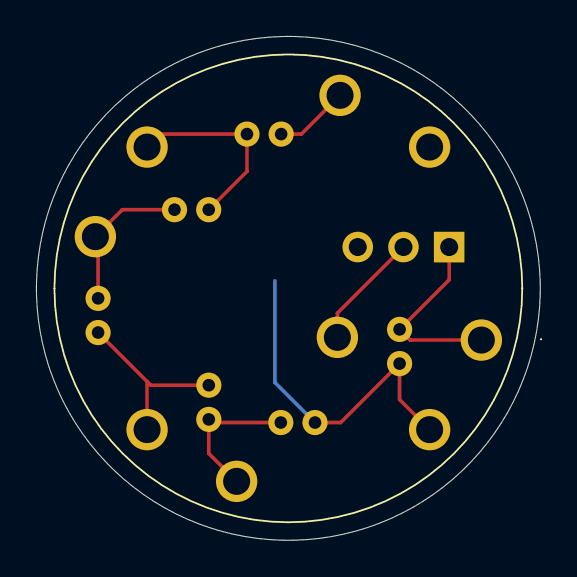
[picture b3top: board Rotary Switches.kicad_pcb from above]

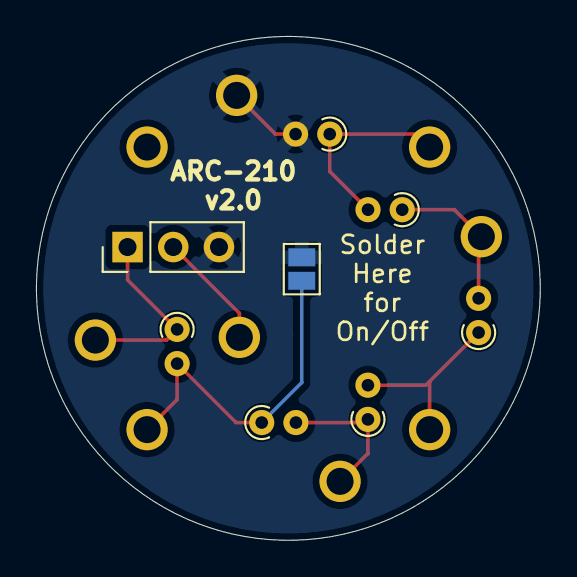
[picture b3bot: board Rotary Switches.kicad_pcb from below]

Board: 2 copper layers, 28.0 x 28.0 mm, 9 parts (8 on the bottom side), 8 nets.
